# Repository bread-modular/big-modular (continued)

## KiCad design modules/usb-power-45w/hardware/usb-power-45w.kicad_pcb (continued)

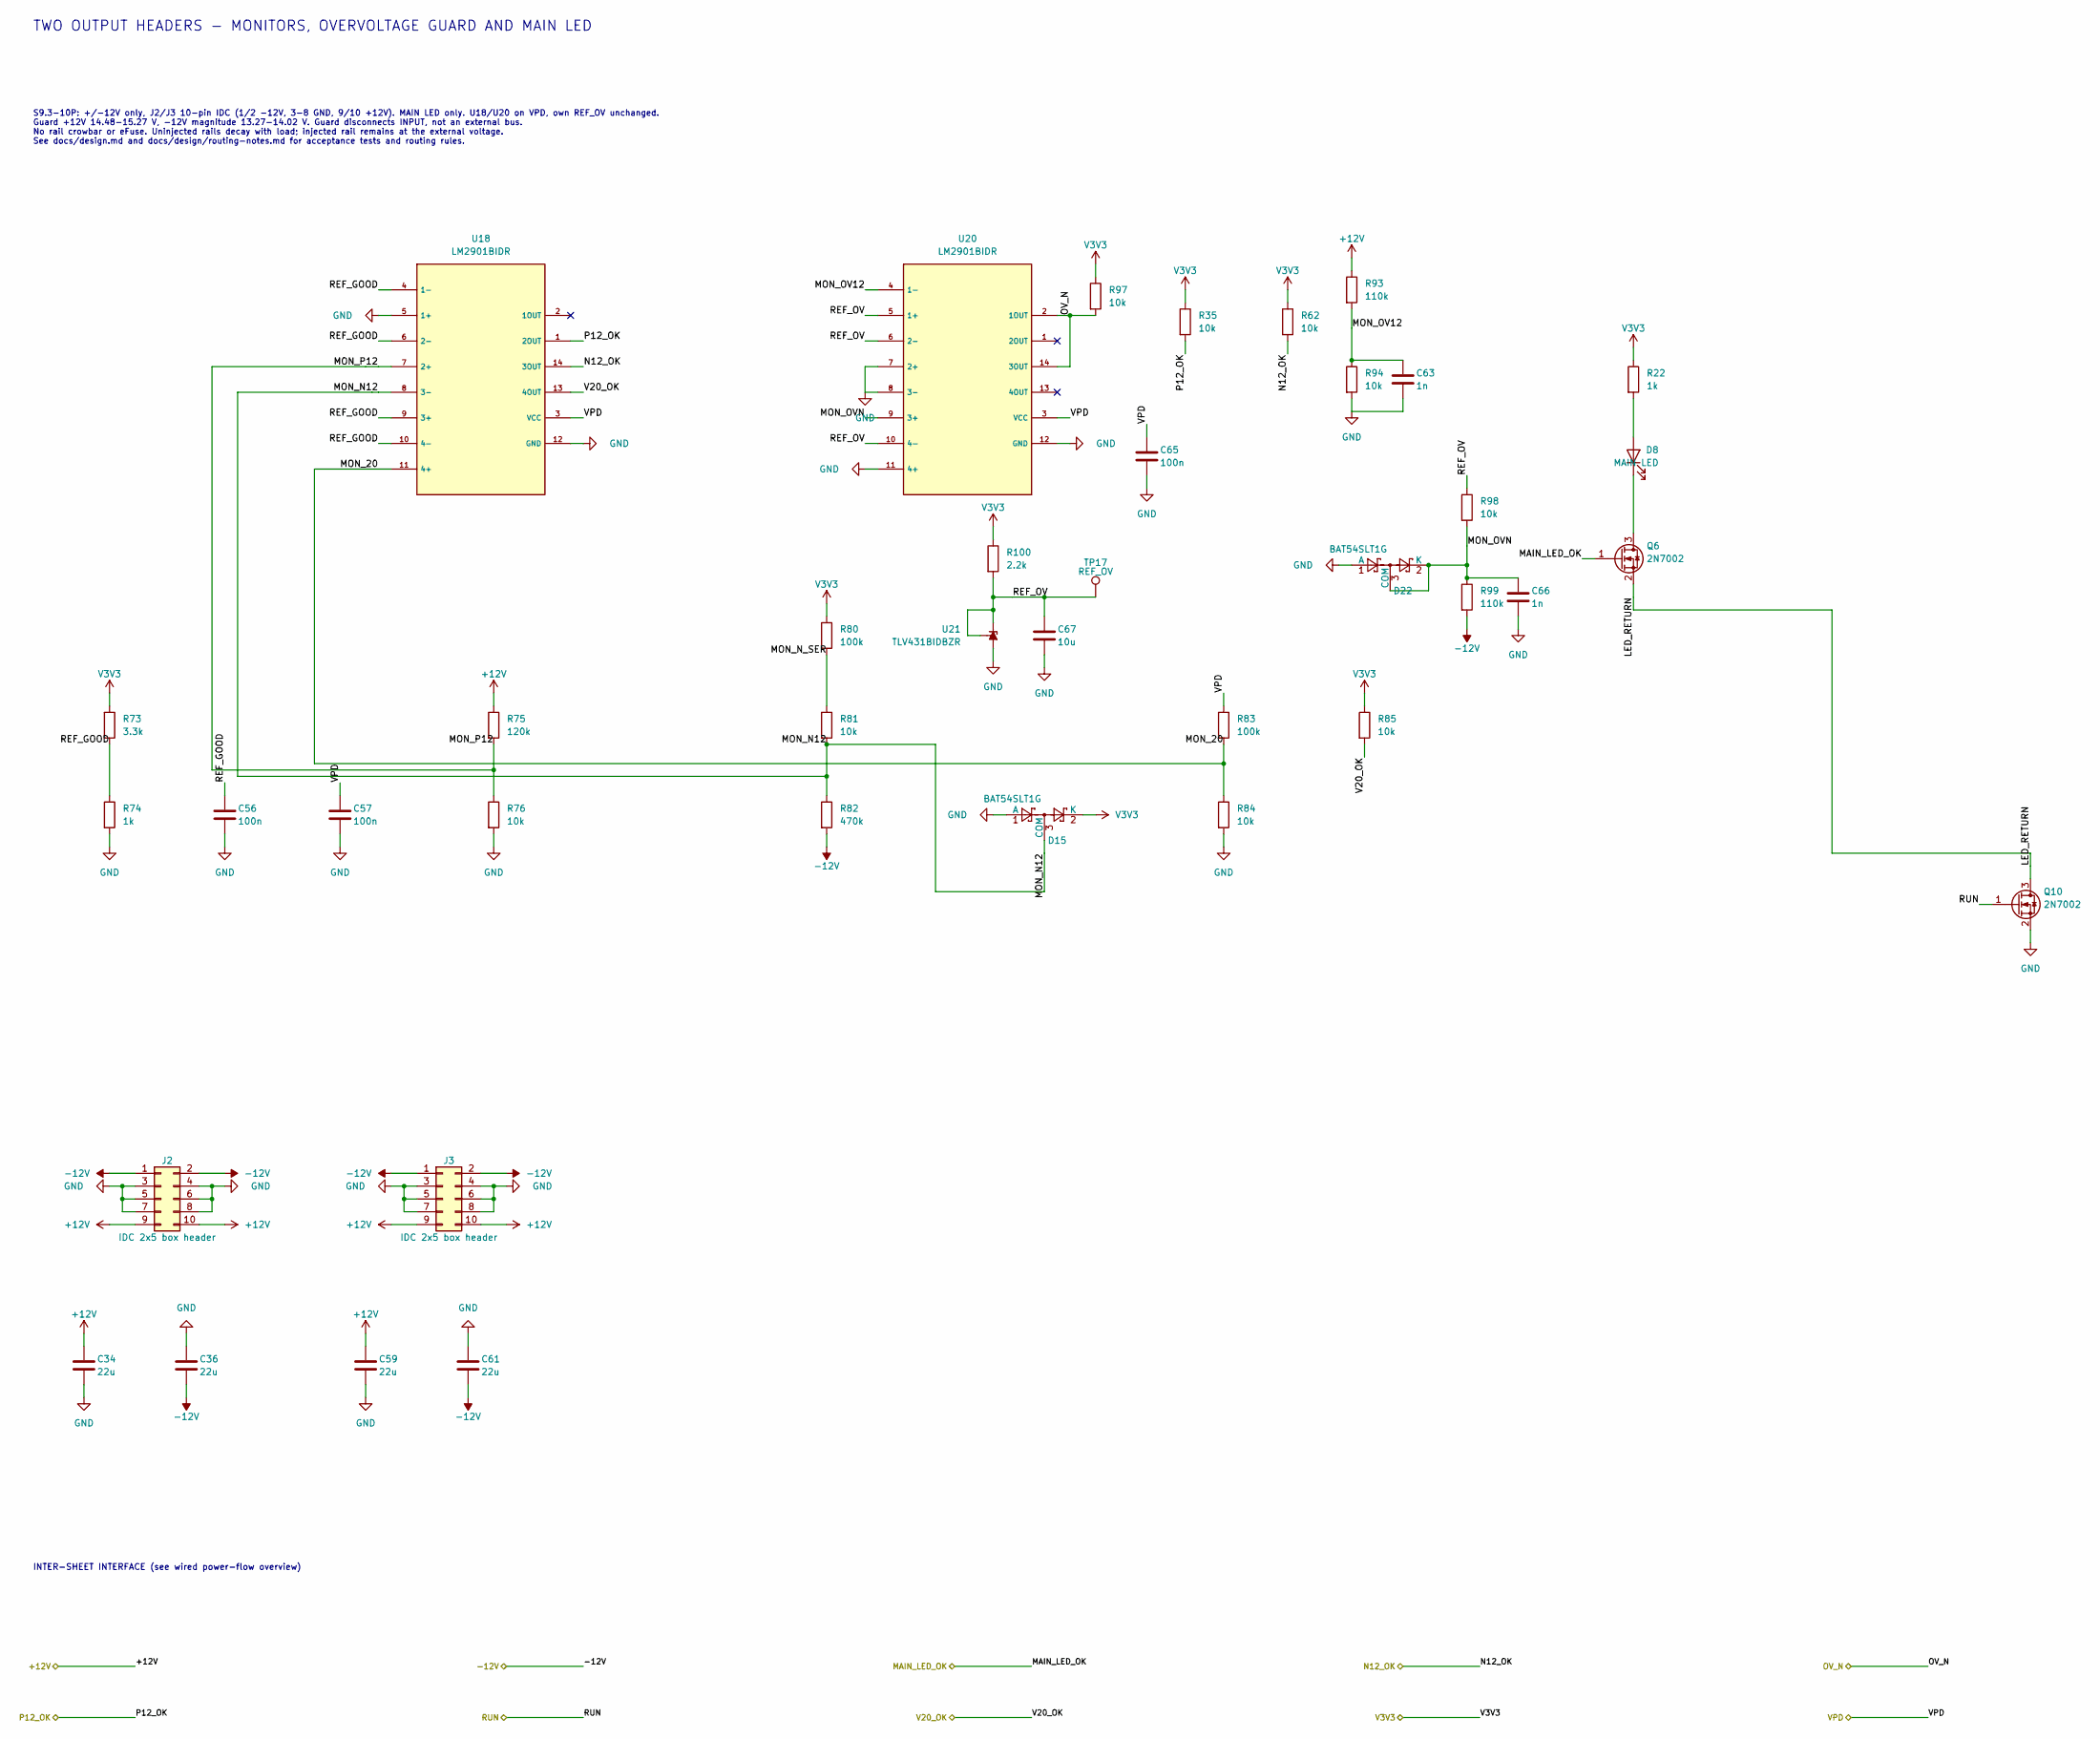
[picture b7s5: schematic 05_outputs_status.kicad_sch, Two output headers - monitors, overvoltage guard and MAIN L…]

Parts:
C34, C36, C59, C61: 22u; C_1206_3216Metric; Voltage 25V; MPN CL31A226KAHNNNE; LCSC C12891
C56, C57, C65: 100n; C_0603_1608Metric; Voltage 50V; MPN CC0603KRX7R9BB104; LCSC C14663
C63, C66: 1n; C_0603_1608Metric; Voltage 50V; MPN CL10B102KB8NNNC; LCSC C1588
C67: 10u; C_0603_1608Metric; Voltage 10V; MPN CL10A106KP8NNNC; LCSC C19702
D8: MAIN LED; LED_D3.0mm_Horizontal_O1.27mm_Z2.0mm_Edge
D15, D22: BAT54SLT1G; SOT-23; MPN BAT54SLT1G; LCSC C19726
J2, J3: IDC 2x5 box header; IDC-Header_2x05_P2.54mm_Vertical_Wurth_61201021621; MPN 61201021621
Q6, Q10: 2N7002; SOT-23; MPN 2N7002; LCSC C8545
R22, R74: 1k; R_0603_1608Metric; Tolerance 1%; MPN 0603WAF1001T5E; LCSC C21190
R35, R62, R76, R81, R84, R85, R97: 10k; R_0603_1608Metric; Tolerance 1%; MPN 0603WAF1002T5E; LCSC C25804
R73: 3.3k; R_0603_1608Metric; Tolerance 1%; MPN 0603WAF3301T5E; LCSC C22978
R75: 120k; R_0603_1608Metric; Tolerance 1%; MPN 0603WAF1203T5E; LCSC C25808
R80, R83: 100k; R_0603_1608Metric; Tolerance 1%; MPN 0603WAF1003T5E; LCSC C25803
R82: 470k; R_0603_1608Metric; Tolerance 1%; MPN 0603WAF4703T5E; LCSC C23178
R93, R99: 110k; R_0603_1608Metric; Tolerance 0.1%; MPN RT0603BRD07110KL; LCSC C326736
R94, R98: 10k; R_0603_1608Metric; Tolerance 0.1%; MPN RT0603BRD0710KL; LCSC C95204
R100: 2.2k; R_0603_1608Metric; Tolerance 1%; MPN 0603WAF2201T5E; LCSC C4190
TP17: REF_OV; TestPoint_Pad_D1.0mm
U18, U20: LM2901BIDR; SOIC-14_3.9x8.7mm_P1.27mm; MPN LM2901BIDR; LCSC C22427890
U21: TLV431BIDBZR; SOT-23; MPN TLV431BIDBZR; LCSC C398375

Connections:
+12V: C34.1, C59.1, J2.9, J2.10, J3.9, J3.10, R75.1, R93.1; also elsewhere on the board
-12V: C36.2, C61.2, J2.1, J2.2, J3.1, J3.2, R82.2, R99.2; also elsewhere on the board
/MAIN_LED_OK: Q6.1 (G); also elsewhere on the board
/N12_OK: R62.2, U18.14 (3OUT); also elsewhere on the board
/OV_N: R97.2, U20.2 (1OUT), U20.14 (3OUT); also elsewhere on the board
/P12_OK: R35.2, U18.1 (2OUT); also elsewhere on the board
/RUN: Q10.1 (G); also elsewhere on the board
/Two output headers - monitors, overvoltage guard and MAIN LED/LED_RETURN: Q6.2 (S), Q10.3 (D)
/Two output headers - monitors, overvoltage guard and MAIN LED/MON_20: R83.2, R84.1, U18.11 (4+)
/Two output headers - monitors, overvoltage guard and MAIN LED/MON_N12: D15.3 (COM), R81.2, R82.1, U18.8 (3-)
/Two output headers - monitors, overvoltage guard and MAIN LED/MON_N_SER: R80.2, R81.1
/Two output headers - monitors, overvoltage guard and MAIN LED/MON_OV12: C63.1, R93.2, R94.1, U20.4 (1-)
/Two output headers - monitors, overvoltage guard and MAIN LED/MON_OVN: C66.1, D22.2 (K), D22.3 (COM), R98.2, R99.1, U20.9 (3+)
/Two output headers - monitors, overvoltage guard and MAIN LED/MON_P12: R75.2, R76.1, U18.7 (2+)
/Two output headers - monitors, overvoltage guard and MAIN LED/REF_GOOD: C56.1, R73.2, R74.1, U18.4 (1-), U18.6 (2-), U18.9 (3+), U18.10 (4-)
/Two output headers - monitors, overvoltage guard and MAIN LED/REF_OV: C67.1, R98.1, R100.2, TP17.1 (1_1), U20.5 (1+), U20.6 (2-), U20.10 (4-), U21.1 (REF), U21.2 (K)
/V20_OK: R85.2, U18.13 (4OUT); also elsewhere on the board
/VPD: C57.1, C65.1, R83.1, U18.3 (VCC), U20.3 (VCC); also elsewhere on the board
GND: C34.2, C36.1, C56.2, C57.2, C59.2, C61.1, C63.2, C65.2, C66.2, C67.2, D15.1 (A), D22.1 (A), J2.3, J2.4, J2.5, J2.6, J2.7, J2.8, J3.3, J3.4, J3.5, J3.6, J3.7, J3.8, Q10.2 (S), R74.2, R76.2, R84.2, R94.2, U18.5 (1+), U18.12 (GND), U20.7 (2+), U20.8 (3-), U20.11 (4+), U20.12 (GND), U21.3 (A); also elsewhere on the board
unnamed: D8.2 (A), R22.2
unnamed: D8.1 (K), Q6.3 (D)
V3V3: D15.2 (K), R22.1, R35.1, R62.1, R73.1, R80.1, R85.1, R97.1, R100.1; also elsewhere on the board

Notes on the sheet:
TWO OUTPUT HEADERS - MONITORS, OVERVOLTAGE GUARD AND MAIN LED
INTER-SHEET INTERFACE (see wired power-flow overview)
S9.3-10P: +/-12V only, J2/J3 10-pin IDC (1/2 -12V, 3-8 GND, 9/10 +12V). MAIN LED only. U18/U20 on VPD, own REF_OV unchanged. Guard +12V 14.48-15.27 V, -12V magnitude 13.27-14.02 V. Guard disconnects INPUT, not an external bus. No rail crowbar or eFuse. Uninjected rails decay with load; injected rai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

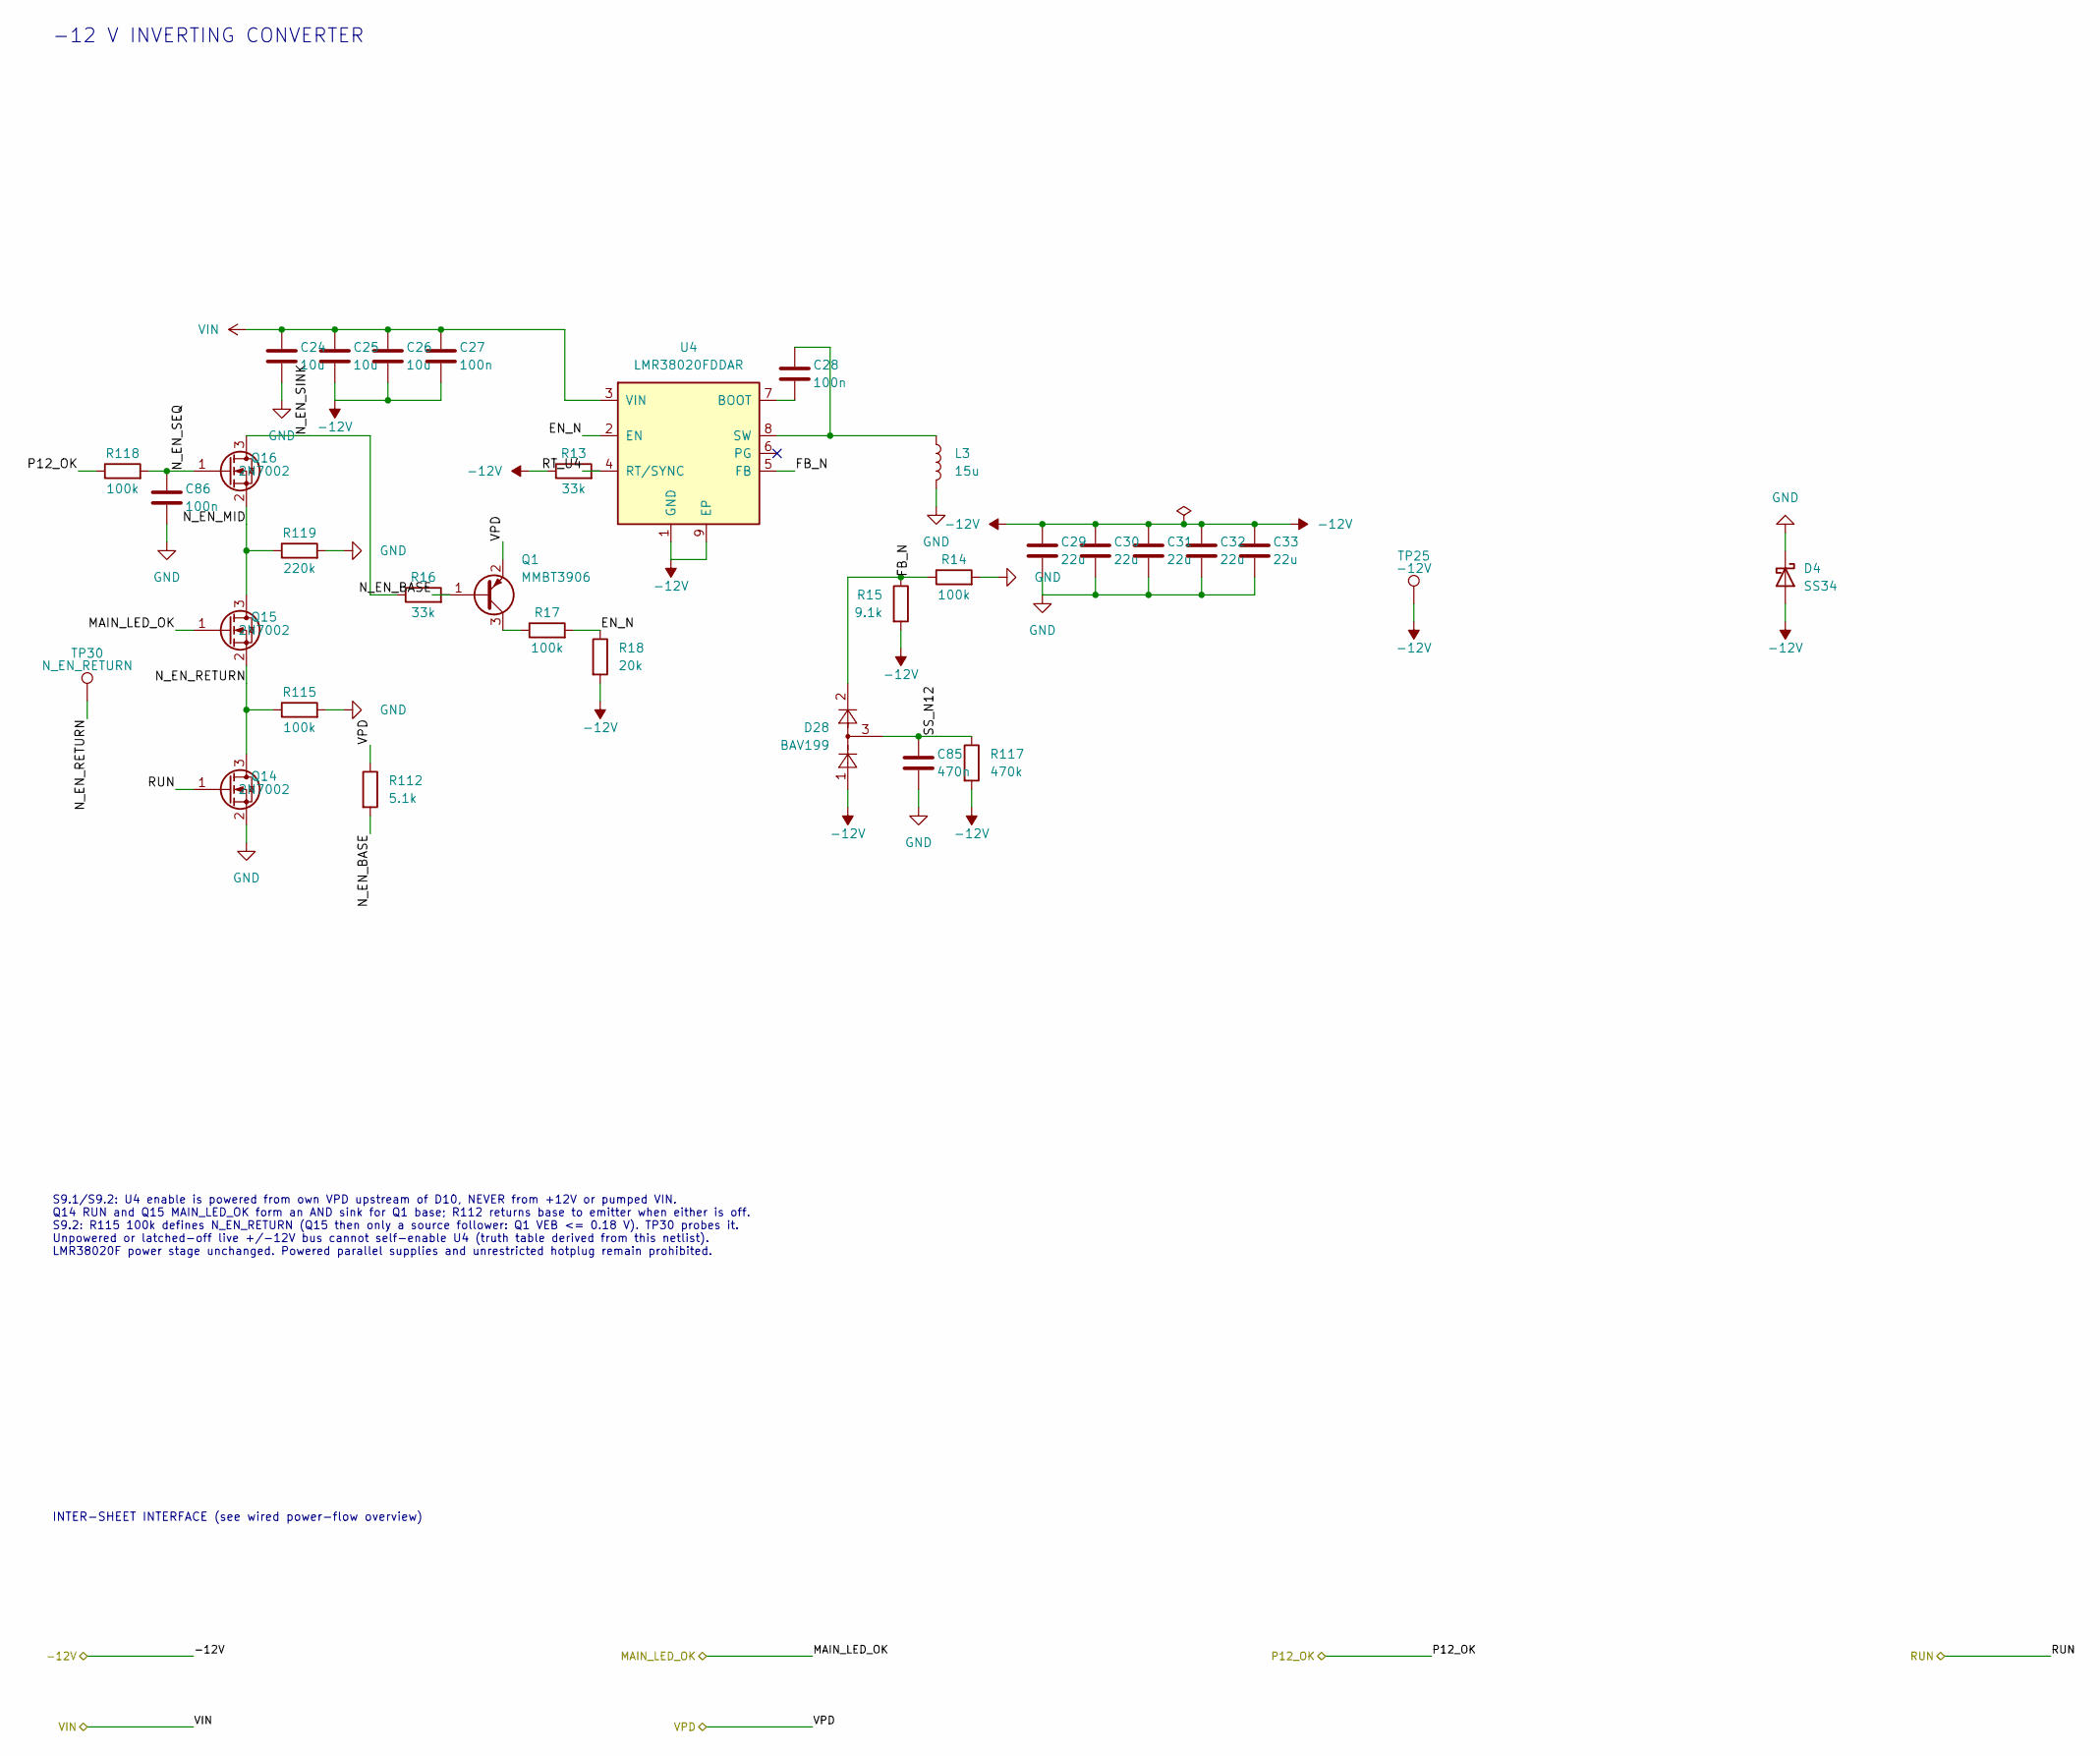
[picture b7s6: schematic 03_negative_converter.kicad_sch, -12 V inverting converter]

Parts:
C24, C25, C26: 10u; C_1206_3216Metric; Voltage 50V; MPN CL31A106KBHNNNE; LCSC C13585
C27, C28, C86: 100n; C_0603_1608Metric; Voltage 50V; MPN CC0603KRX7R9BB104; LCSC C14663
C29, C30, C31, C32, C33: 22u; C_1206_3216Metric; Voltage 25V; MPN CL31A226KAHNNNE; LCSC C12891
C85: 470n; C_0603_1608Metric; Voltage 25V; MPN CL10B474KA8NNNC; LCSC C1623
D4: SS34; D_SMA; MPN SS34; LCSC C8678
D28: BAV199; SOT-23; MPN BAV199LT1G; LCSC C145516
L3: 15u; L_SLO1040H6R8MTT; MPN SLO1040H150MTT; LCSC C182184
Q1: MMBT3906; SOT-23; MPN MMBT3906LT1G; LCSC C53444
Q14, Q15, Q16: 2N7002; SOT-23; MPN 2N7002; LCSC C8545
R13, R16: 33k; R_0603_1608Metric; Tolerance 1%; MPN 0603WAF3302T5E; LCSC C4216
R14, R17, R115, R118: 100k; R_0603_1608Metric; Tolerance 1%; MPN 0603WAF1003T5E; LCSC C25803
R15: 9.1k; R_0603_1608Metric; Tolerance 1%; MPN 0603WAF9101T5E; LCSC C23260
R18: 20k; R_0603_1608Metric; Tolerance 1%; MPN 0603WAF2002T5E; LCSC C4184
R112: 5.1k; R_0603_1608Metric; Tolerance 1%; MPN 0603WAF5101T5E; LCSC C23186
R117: 470k; R_0603_1608Metric; Tolerance 1%; MPN 0603WAF4703T5E; LCSC C23178
R119: 220k; R_0603_1608Metric; Tolerance 1%; MPN 0603WAF2203T5E; LCSC C22961
TP25: -12V; TestPoint_Pad_D1.5mm
TP30: N_EN_RETURN; TestPoint_Pad_D1.5mm
U4: LMR38020FDDAR; TI_SO-PowerPAD-8_NoViaInPad; MPN LMR38020FDDAR; LCSC C5149193

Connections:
-12V: C25.2, C26.2, C27.2, C29.1, C30.1, C31.1, C32.1, C33.1, D4.2 (A), D28.1 (A), R13.1, R15.2, R18.2, R117.2, TP25.1 (1_1), U4.1 (GND), U4.9 (EP); also elsewhere on the board
/-12 V inverting converter/EN_N: R17.2, R18.1, U4.2 (EN)
/-12 V inverting converter/FB_N: D28.2 (K), R14.1, R15.1, U4.5 (FB)
/-12 V inverting converter/N_EN_BASE: Q1.1 (B), R16.2, R112.2
/-12 V inverting converter/N_EN_MID: Q15.3 (D), Q16.2 (S), R119.1
/-12 V inverting converter/N_EN_RETURN: Q14.3 (D), Q15.2 (S), R115.1, TP30.1 (1_1)
/-12 V inverting converter/N_EN_SEQ: C86.1, Q16.1 (G), R118.2
/-12 V inverting converter/N_EN_SINK: Q16.3 (D), R16.1
/-12 V inverting converter/RT_U4: R13.2, U4.4 (RT/SYNC)
/-12 V inverting converter/SS_N12: C85.1, D28.3 (COM), R117.1
/MAIN_LED_OK: Q15.1 (G); also elsewhere on the board
/P12_OK: R118.1; also elsewhere on the board
/RUN: Q14.1 (G); also elsewhere on the board
/VPD: Q1.2 (E), R112.1; also elsewhere on the board
GND: C24.2, C29.2, C30.2, C31.2, C32.2, C33.2, C85.2, C86.2, D4.1 (K), L3.2, Q14.2 (S), R14.2, R115.2, R119.2; also elsewhere on the board
unnamed: Q1.3 (C), R17.1
unnamed: C28.2, U4.7 (BOOT)
unnamed: C28.1, L3.1, U4.8 (SW)
VIN: C24.1, C25.1, C26.1, C27.1, U4.3 (VIN); also elsewhere on the board

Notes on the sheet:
-12 V INVERTING CONVERTER
INTER-SHEET INTERFACE (see wired power-flow overview)
S9.1/S9.2: U4 enable is powered from own VPD upstream of D10, NEVER from +12V or pumped VIN. Q14 RUN and Q15 MAIN_LED_OK form an AND sink for Q1 base; R112 returns base to emitter when either is off. S9.2: R115 100k defines N_EN_RETURN (Q15 then only a source follower: Q1 VEB <= 0.18 V). TP30 probe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

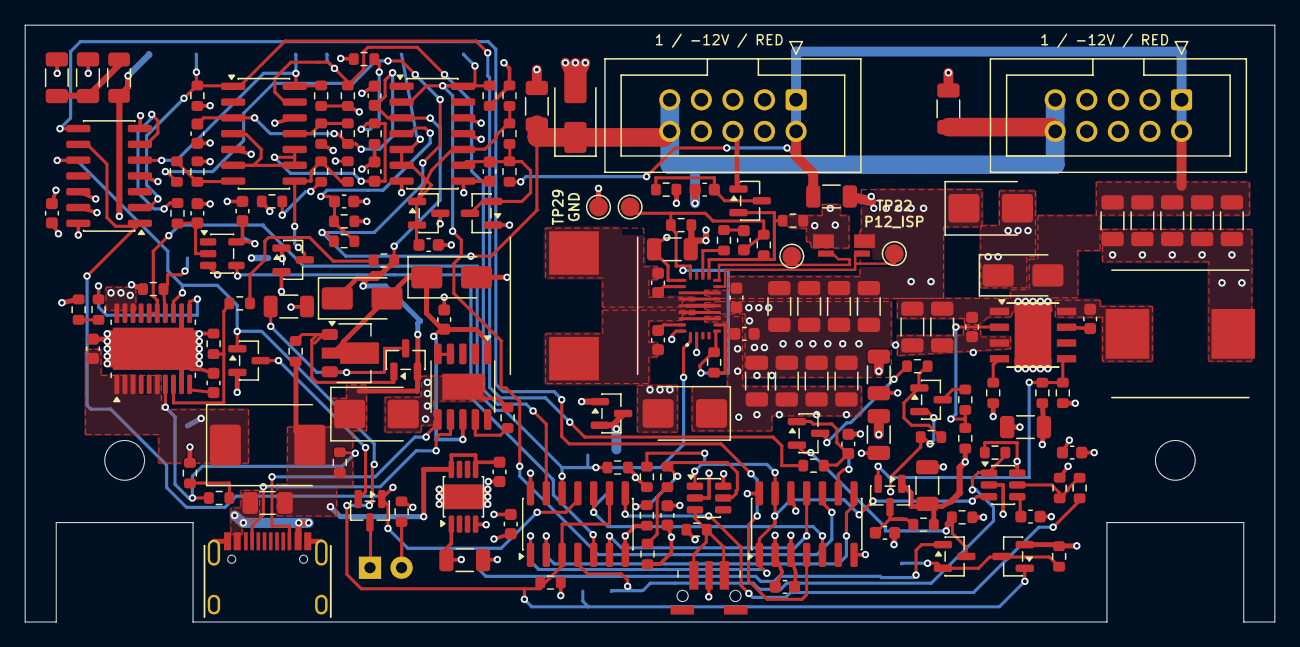
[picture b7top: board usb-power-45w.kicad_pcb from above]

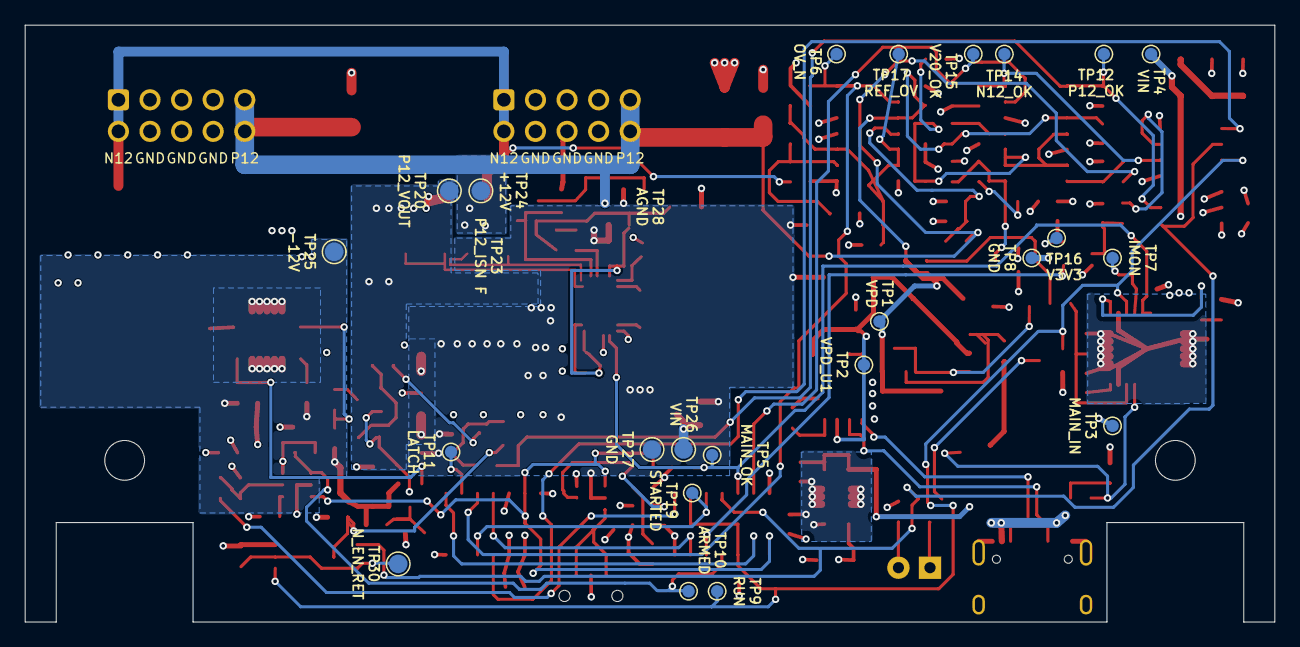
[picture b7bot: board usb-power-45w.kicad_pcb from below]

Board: 4 copper layers, 100.5 x 48.0 mm, 185 parts (23 on the bottom side), 84 nets.

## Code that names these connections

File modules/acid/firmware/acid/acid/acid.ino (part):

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// ----------------------------------------------------------------------------
// ACID — Bread Modular MCO + ENV on one ATtiny1616 (../../docs/research.md 3).
//
//   * MCO (BM 1.0.1, as modules/low): MIDI note-on sets tone 1 (PB4) and the
//     detuned tone 2 (PB5); DETUNE (PB0) puts tone 2 0..12 semitones below.
//   * ENV (BM 1.2.1): MIDI note on/off is the gate of the envelope on the DAC
//     (PA6 -> ENV_CV: SVF CV normal and ENV OUT). ATTACK (PA1, hold in HR) and
//     RELEASE (PA2) set the times, plus MIDI CC22 / CC75 as BM. MODE (PC0,
//     a click) cycles HR / AR / ASR, stored in EEPROM; the selected model's
//     LED (PC1 / PA4 / PA5) follows the envelope: its brightness tracks the
//     envelope level, up to 10 %; after power-up or a MODE change it is lit
//     at 10 % for 1 s to show the selection.
//   * REC (PC2 / LED PC3): 4-bar ATTACK/RELEASE motion recorder on MIDI clock
//     (shared lib/CvRecorder, as the 8bit crash): click to record (LED blinks),
//     after 4 bars it loops (LED solid), click again for the live knobs.
// ----------------------------------------------------------------------------

// JP1 on the ACID carrier picks the MIDI input path (set by ../../jumper.sh):
//   P (protected) = 8bit / MIDI V2 NPN front end, which inverts the UART data -> 1
//   D (direct)    = jack tip straight to PB3, as Bread Modular             -> 0
#ifndef MIDI_RX_INVERT
#error "MIDI_RX_INVERT must be set: build with ../../compile.sh p|d"
#endif

#define DETUNE_INPUT_PIN PIN_PB0
#define PIN_CV1          PIN_PA1   // ATTACK knob (hold time in HR)
#define PIN_CV2          PIN_PA2   // RELEASE knob
#define MODE_BUTTON_PIN  PIN_PC0   // envelope model (BM ENV algo button)
#define LED_HR           PIN_PC1
#define LED_AR           PIN_PA4
#define LED_ASR          PIN_PA5
#define REC_BUTTON_PIN   PIN_PC2   // BM ENV gate-mode button
#define REC_LED_PIN      PIN_PC3

#define ALGO_HOLD_RELEASE 0
#define ALGO_ATTACK_RELEASE 1
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#define KNOB_READ_MS 2             // knob reads off the envelope's hot loop

// MODE LED brightness: TCA0 in split mode (TCB0/TCB1 are the tones, TCD0 is
// millis), 20 MHz / 256 / 256 = 305 Hz, duty = count / 256. PA4 (WO4, HCMP1)
// and PA5 (WO5, HCMP2) are hardware PWM. PC1 has no TCA output, so the low
// counter switches it in software (LCMP0 on, LUNF off); those two interrupts
// run only while the HR LED is lit.
#define LED_MAX_PERCENT 10         // brightness at full envelope level
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EnvelopeGenerator *envelope;

ToggleMode algoMode(MODE_BUTTON_PIN, 1, 3);        // EEPROM index 1, as BM
CvRecorder recorder(REC_BUTTON_PIN, REC_LED_PIN);

const uint8_t modeLeds[3] = {LED_HR, LED_AR, LED_ASR};

float detunedSemitones = 0;
uint16_t liveCV1 = 0;              // ATTACK / RELEASE knobs (recorder input)
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int modCV2 = 0;                    // MIDI CC75 (release time)

bool midiGate = false;
byte gateNote = 0;                 // note that holds the gate
byte selectedLed = 0;              // index into modeLeds
unsigned long modeShownAt = 0;     // millis() of the last selection change

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  TCA0.SPLIT.CTRLA = TCA_SPLIT_CLKSEL_DIV256_gc | TCA_SPLIT_ENABLE_bm;
}

// PC1 (HR) software PWM: the down-counting low counter matches LCMP0 =
// duty - 1, so PC1 is high for duty counts until the underflow.
ISR(TCA0_LCMP0_vect) {
  PORTC.OUTSET = PIN1_bm;
  TCA0.SPLIT.INTFLAGS = TCA_SPLIT_LCMP0_bm;
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
  uint8_t outputs = 0;
  if (duty && led == 1) {
    outputs = TCA_SPLIT_HCMP1EN_bm;    // PA4 (AR)
  } else if (duty && led == 2) {
    outputs = TCA_SPLIT_HCMP2EN_bm;    // PA5 (ASR)
  }
  TCA0.SPLIT.CTRLB = outputs;

  const bool soft = duty && led == 0;  // PC1 (HR)
  TCA0.SPLIT.INTCTRL = soft ? TCA_SPLIT_LUNF_bm | TCA_SPLIT_LCMP0_bm : 0;
  if (!soft) {
    PORTC.OUTCLR = PIN1_bm;
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}

void handleNoteOff(byte channel, byte note, byte velocity) {
  // Only the latest note closes the gate: an overlapping (legato) note keeps
  // the envelope open instead of releasing it under the held note.
  if (note == gateNote) {
    midiGate = false;
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  MIDI.begin(1);
#if MIDI_RX_INVERT
  // JP1 = P: the NPN input stage inverts the MIDI UART data, so invert
  // PB3 (RX) in the port before the USART samples it.
  PORTB.PIN3CTRL |= PORT_INVEN_bm;
#endif
  MIDI.setHandleNoteOn(handleNoteOn);
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  (void)analogRead(PIN_CV1);       // throwaway warm-up read
  readKnobs();

  // DAC0 setup for the envelope via the PA6 pin
  VREF.CTRLA |= VREF_DAC0REFSEL_4V34_gc; //this will force it to use VDD as the VREF
  VREF.CTRLB |= VREF_DAC0REFEN_bm;
  DAC0.CTRLA = DAC_ENABLE_bm | DAC_OUTEN_bm;
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
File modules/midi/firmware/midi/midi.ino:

/* Arduino ATTiny 1616 Pin Map

  0 - PA4
  1 - PA5
  2 - PA6
  3 - PA7
  4 - PB5
  5 - PB4
  6 - PB3, RX
  7 - PB2, TX
  8 - PB1
  9 - PB0
  10 - PC0
  11 - PC1
  12 - PC2
  13 - PC3
  14 - PA1
  15 - PA2
  16 - PA3
*/

#include "SimpleMIDI.h"
#include <SoftwareSerial.h>

// Hardware version, set by ../compile.sh / ../flash.sh (v1 | v2 | v2-direct).
//   1 = V1 (hardware/v1): Bread Modular V1 direct input, JP1 -> PB3.
//   2 = V2 (hardware/v2): protected NPN input (Q1). It inverts the UART, so
//       PB3 needs PORT_INVEN (like the Bread Modular midi-2.0 6N137 firmware).
#ifndef MIDI_HW_VERSION
#error "MIDI_HW_VERSION is not set: build with ./compile.sh v1|v2|v2-direct"
#endif

// Invert RX (PB3). Defaults from the version; v2-direct sets 0 for a V2 board
// with JP2 bridged 2-3 (MIDI_IN straight to PB3, the V1 debug path).
#ifndef MIDI_RX_INVERT
#if MIDI_HW_VERSION == 1
#define MIDI_RX_INVERT 0
#elif MIDI_HW_VERSION == 2
#define MIDI_RX_INVERT 1
#else
#error "MIDI_HW_VERSION must be 1 or 2"
#endif
#endif

// Compile-time MIDI channel start (1-indexed).
// Default: respond to incoming MIDI channels 1-8.
// Override via a .config file (e.g. MIDI_CHAN_START=9 → channels 9-16).
#ifndef MIDI_CHAN_START
#define MIDI_CHAN_START 1
#endif

#define MIDI_CHAN_OFFSET (MIDI_CHAN_START - 1)

#define PIN_RX 6 // PB3
#define PIN_TX 7 // PB2

// Define the Gate Pins
#define GATE_PIN_01 10 // PC0
#define GATE_PIN_02 11 // PC1
#define GATE_PIN_03 12 // PC2
#define GATE_PIN_04 13 // PC3
#define GATE_PIN_05 14 // PA1
#define GATE_PIN_06 15 // PA2
#define GATE_PIN_07 16 // PA3
#define GATE_PIN_08 0 // PA4

// Define IMIDI Pins
#define IMIDI_PIN_01 1 // PA5
#define IMIDI_PIN_02 2 // PA6
#define IMIDI_PIN_03 3 // PA7
#define IMIDI_PIN_04 4 // PB5
#define IMIDI_PIN_05 5 // PB4
#define IMIDI_PIN_06 8 // PB1
#define IMIDI_PIN_07 9 // PB0

// Channel LED brightness, as the MCC bank LEDs: software PWM on the LED pins
// (no hardware PWM on all of them). TCB0 ticks at 20 kHz; LED_PWM_STEPS ticks
// = 200 Hz PWM, LED_ON_STEPS of them on.
#define LED_PWM_STEPS 100
#define LED_ON_STEPS 3      // 3 % brightness
#define LED_PORTC_MASK (PIN0_bm | PIN1_bm | PIN2_bm | PIN3_bm)  // CH1-CH4
#define LED_PORTA_MASK (PIN1_bm | PIN2_bm | PIN3_bm | PIN4_bm)  // CH5-CH8
constexpr uint16_t LED_TCB_COMPARE = (F_CPU / 2) / 20000 - 1;
volatile uint8_t ledMaskC = 0;  // PORTC bits of the lit channel LEDs
volatile uint8_t ledMaskA = 0;  // PORTA bits of the lit channel LEDs

// Create a MIDI object
SimpleMIDI MIDI;

SoftwareSerial midiSerialArray[] = {
    SoftwareSerial(-1, IMIDI_PIN_01),
    SoftwareSerial(-1, IMIDI_PIN_02),
    SoftwareSerial(-1, IMIDI_PIN_03),
    SoftwareSerial(-1, IMIDI_PIN_04),
    SoftwareSerial(-1, IMIDI_PIN_05),
    SoftwareSerial(-1, IMIDI_PIN_06),
    SoftwareSerial(-1, IMIDI_PIN_07),
};

int getGatePin(int id) {
  switch (id) {
    case 0:
      return GATE_PIN_01;
    case 1:
      return GATE_PIN_02;
    case 2:
      return GATE_PIN_03;
    case 3:
      return GATE_PIN_04;
    case 4:
      return GATE_PIN_05;
    case 5:
      return GATE_PIN_06;
    case 6:
      return GATE_PIN_07;
    case 7:
      return GATE_PIN_08;
    default:
      return -1;
  }
}

// Map an incoming MIDI channel (0-15) to a local output/gate index (0-7),
// or -1 if the channel is outside the configured range.
int getOutputIndex(byte channel) {
  int idx = (int)channel - MIDI_CHAN_OFFSET;
  if (idx < 0 || idx > 7) {
    return -1;
  }
  return idx;
}

// Port bit of channel LED `id` (0-7): CH1-CH4 on PC0-PC3, CH5-CH8 on PA1-PA4.
uint8_t getLedBit(int id) {
  return id < 4 ? (1 << id) : (1 << (id - 3));
}

void setLed(int id, bool on) {
  const uint8_t bit = getLedBit(id);
  volatile uint8_t &mask = id < 4 ? ledMaskC : ledMaskA;
  uint8_t sreg = SREG;
  cli();
  if (on) {
    mask |= bit;
  } else {
    mask &= ~bit;
    if (id < 4) {
      PORTC.OUTCLR = bit;
    } else {
      PORTA.OUTCLR = bit;
    }
  }
  SREG = sreg;
}

void setupLedPwm() {
  TCB0.CTRLA = TCB_CLKSEL_CLKDIV2_gc;  // 10 MHz
  TCB0.CTRLB = TCB_CNTMODE_INT_gc;     // periodic interrupt
  TCB0.CCMP = LED_TCB_COMPARE;
  TCB0.INTCTRL = TCB_CAPT_bm;
  TCB0.CTRLA |= TCB_ENABLE_bm;
}

ISR(TCB0_INT_vect) {
  static uint8_t step = 0;
  if (++step >= LED_PWM_STEPS) {
    step = 0;
  }
  if (step < LED_ON_STEPS) {
    PORTC.OUTSET = ledMaskC;
    PORTA.OUTSET = ledMaskA;
  } else {
    PORTC.OUTCLR = LED_PORTC_MASK;
    PORTA.OUTCLR = LED_PORTA_MASK;
  }
  TCB0.INTFLAGS = TCB_CAPT_bm;
}

void sendMIDI(byte channel, byte status, byte data1, byte data2) {
  if (channel == 7) {
    Serial.write(status); // Send the status byte
    Serial.write(data1);  // Send the first data byte
    Serial.write(data2);  // Send the second data byte
    return;
  }

  int channelIndex = channel;
  if (channelIndex >= 0 && channelIndex < 7) {
    SoftwareSerial &serialCh = midiSerialArray[channelIndex];
    serialCh.write(status); // Send the status byte
    serialCh.write(data1);  // Send the first data byte
    serialCh.write(data2);  // Send the second data byte
  }
}

void sendMIDIRealtime(byte realtimeByte) {
  for (int i = 0; i < 7; i++) {
    midiSerialArray[i].write(realtimeByte);
  }

  // This is for the channel 8
  Serial.write(realtimeByte);
}

void setupGates() {
  for (int x = 0; x < 8; x = x + 1) {
    int gatePin = getGatePin(x);
    pinMode(gatePin, OUTPUT);
    digitalWrite(gatePin, LOW);
  }
  setupLedPwm();
}

void setupIMIDI() {
  pinMode(IMIDI_PIN_01, OUTPUT);
  pinMode(IMIDI_PIN_02, OUTPUT);
  pinMode(IMIDI_PIN_03, OUTPUT);
  pinMode(IMIDI_PIN_04, OUTPUT);
  pinMode(IMIDI_PIN_05, OUTPUT);
  pinMode(IMIDI_PIN_06, OUTPUT);
  pinMode(IMIDI_PIN_07, OUTPUT);

  for (int i = 0; i < 7; i++) {
    midiSerialArray[i].begin(31250); // Start each SoftwareSerial at MIDI baud rate
  }
}

void handleNoteOn(byte channel, byte note, byte velocity) {
  int idx = getOutputIndex(channel);
  if (idx == -1) {
    return;
  }

  setLed(idx, true);

  sendMIDI(idx, 0x90, note, velocity);
}

// Callback for Note Off messages
void handleNoteOff(byte channel, byte note, byte velocity) {
  int idx = getOutputIndex(channel);
  if (idx == -1) {
    return;
  }

  setLed(idx, false);

  sendMIDI(idx, 0x80, note, velocity);
}

// Callback for handling CC messages
void handleControlChange(byte channel, byte controller, byte value) {
  int idx = getOutputIndex(channel);
  if (idx == -1) {
    return;
  }

  sendMIDI(idx, 0xB0, controller, value);
}

void handleRealtime(byte realtimeType) {
  sendMIDIRealtime(realtimeType);
}

void setup() {
  setupGates();

  // Initialize the MIDI library
  MIDI.begin(31250);
  MIDI.setNoteOnCallback(handleNoteOn);
  MIDI.setNoteOffCallback(handleNoteOff);
  MIDI.setControlChangeCallback(handleControlChange);
  MIDI.setRealtimeCallback(handleRealtime);

#if MIDI_RX_INVERT
  // V2 NPN input stage inverts the MIDI UART data, so tell the port to
  // invert PB3 (RX) before the USART samples it.
  PORTB.PIN3CTRL |= PORT_INVEN_bm;
#endif

  setupIMIDI();

  Serial.println("MIDI Listening Started!");
}

void loop() {
  MIDI.update();
}

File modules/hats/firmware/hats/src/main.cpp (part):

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// HATS S4 firmware (STM32G071C8T6 U2): Bread Modular NOISE + HIHAT on one
// MCU, plus the PWM CUTOFF vactrol and the shared 4-bar REC recorder.
//
//   PA4 DAC1_OUT1  white noise (BM NOISE, -> R6 / U4A, blue high-pass)
//   PA5 DAC1_OUT2  velocity (BM HIHAT)
//   PA2 / PA3      gate / open hat (BM HIHAT: notes > 60 open)
//   PA1 ADC_IN1    NOISE TONE knob (RV1)
//   PA6 ADC_IN6    CUTOFF knob (RV3)
//   PB0 TIM3_CH3   CUTOFF vactrol LED PWM (R51 -> U11), 31.25 kHz, dithered
//   PB4 / PB5      REC button (pull-up) / REC LED (R48 -> D6)
//   PB7 USART1_RX  MIDI 31250 baud, all channels; RXINV for JP1 = P
//
//   REC (shared CvRecorder): lane 1 CUTOFF, lane 2 NOISE TONE, 4 bars on
//   MIDI clock. MIDI CC 74 x 8 adds to NOISE TONE (BM).
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
// JP1 on the HATS carrier picks the MIDI input path (set by ../jumper.sh):
//   P (protected) = NPN front end (Q1), which inverts the UART data -> 1
//   D (direct)    = jack tip straight to PB7, as Bread Modular     -> 0
#ifndef MIDI_RX_INVERT
#error "MIDI_RX_INVERT must be set: build with ../compile.sh p|d"
#endif

#define GATE_PIN       PIN_PA(2)
#define OPEN_HAT_PIN   PIN_PA(3)
#define REC_BUTTON_PIN PIN_PB(4)
#define REC_LED_PIN    PIN_PB(5)

#define ADC_CH_TONE    1   // PA1
#define ADC_CH_CUTOFF  6   // PA6

static const uint32_t SYSCLK_HZ = 64000000;

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static hats::PwmDither dither;
static hats::MidiParser midi;
static hats::HihatOut hihat;
static CvRecorder recorder(REC_BUTTON_PIN, REC_LED_PIN);

static uint8_t cc74 = 0;
static uint16_t liveCutoff = 0;   // knobs, 0..1023 (recorder input)
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
static void gpioInit() {
    RCC->IOPENR |= RCC_IOPENR_GPIOAEN | RCC_IOPENR_GPIOBEN;
    pinMode(GATE_PIN, OUTPUT);
    pinMode(OPEN_HAT_PIN, OUTPUT);
    digitalWrite(GATE_PIN, LOW);
    digitalWrite(OPEN_HAT_PIN, LOW);
    setMode(GPIOA, 1, 3);   // NOISE TONE, analog
    setMode(GPIOA, 6, 3);   // CUTOFF, analog
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    return (uint16_t)(ADC1->DR >> 2);                // 12 -> 10 bit, as BM analogRead
}

// One scan: PA1 (TONE) then PA6 (CUTOFF).
static void readKnobs() {
    ADC1->CR |= ADC_CR_ADSTART;
    liveTone = adcNext();
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            default:
                continue;
        }
        digitalWrite(GATE_PIN, hihat.gate ? HIGH : LOW);
        digitalWrite(OPEN_HAT_PIN, hihat.open ? HIGH : LOW);
        DAC1->DHR12R2 = hats::dac12(hihat.velocity);
    }
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
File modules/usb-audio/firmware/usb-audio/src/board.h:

// MCU board: clocks, SysTick, pins that are not I2S/I2C, USBHS interrupt.
//
// Pin map (modules/usb-audio/Code.md, MCU board S1):
//   PB6/PB7  USBHS D-/D+          PA9   VBUS sense (10k/20k divider)
//   PB13/PB12/PB15  I2S2 CK/WS/SD (slave RX <- codec SDOUT)
//   PB3/PA15/PB5    I2S3 CK/WS/SD (slave TX -> codec SDIN)
//   PB10/PB11 I2C2 SCL/SDA        PB14  codec RST (10k pull-down on the carrier)
#ifndef BOARD_H_
#define BOARD_H_

#include <stdbool.h>
#include <stddef.h>
#include <stdint.h>

#include "ch32v30x.h"

void board_init(void);
uint32_t board_millis(void);
void board_delay_ms(uint32_t ms);
void board_delay_us(uint32_t us);
bool board_vbus_present(void);
void board_codec_reset(bool asserted);
void board_serial(char *out, size_t len);
void board_reset(void);
// Reset into the DFU bootloader (../bootloader) for ../flash.sh.
void board_reset_to_dfu(void);
// Rewrite + verify the DFU bootloader from RAM (console `blwrite`). Stop I2S first.
bool board_write_bootloader(uint8_t const *img, uint32_t len);
// Settings page: the last 256 bytes of the application area, which the linker
// script leaves free (Makefile). The DFU bootloader erases only the pages it
// writes, so the page survives firmware updates; ../flash.sh --full erases it.
#define BOARD_SETTINGS_BYTES 256u
void const *board_settings(void);
// Erase the page and write `len` bytes (0: erase only), verified. Stop I2S first.
bool board_settings_write(void const *data, uint32_t len);
uint32_t board_crc32(void const *data, uint32_t len);
// Main loop: feeds the bootloader's watchdog and confirms a newly downloaded
// image once the host has kept it configured (../bootloader/src/boot.h).
void board_boot_task(bool configured);

// Critical section against the I2S DMA and USB processing handlers that keeps
// the USBHS capture interrupt (priority 0, board_init) running: masks the
// priorities >= 0x40 through the PFIC threshold.
static inline uint32_t board_irq_mask(void) {
  uint32_t const prev = PFIC->ITHRESDR;
  PFIC->ITHRESDR = 0x40;
  (void) PFIC->ITHRESDR;
  return prev;
}

static inline void board_irq_restore(uint32_t prev) {
  PFIC->ITHRESDR = prev;
}

#endif

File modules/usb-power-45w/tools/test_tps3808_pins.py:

"""TPS3808G01 pin-identity regression (S6 had SENSE=3 / MR=5; TI DBV is MR=3 / SENSE=5).

Run from the repository root (needs kicad-cli; reads, never writes, the module):
  python3 -B -m unittest discover -s modules/usb-power-45w/tools -p 'test_*.py' -v

The old map was self-consistent: symbol, circuit table and verifier table all agreed.
These tests rebuild that state (circuit() and CRIT reverted too) and require the
manufacturer-derived check in verify_design.py to reject it on its own.
"""
import copy
import shutil
import subprocess
import sys
import tempfile
import unittest
import xml.etree.ElementTree as ET
from pathlib import Path
from unittest import mock

sys.path.insert(0, str(Path(__file__).resolve().parent))
import circuit45  # noqa: E402
import verify_design  # noqa: E402
from sexp import parse, nodes, one, walk  # noqa: E402

MODULE = Path(__file__).resolve().parents[1]
HW = MODULE / 'hardware'
OLD_COMMIT = '077905c'          # last commit with the swapped TPS3808 map
OLD_PINS = {'U10': {'1': 'RESET_N', '2': 'GND', '3': 'POR_SENSE', '4': None, '5': 'RESET_BTN_N', '6': 'V3V3'},
            'U11': {'1': 'START_READY', '2': 'GND', '3': 'START_SENSE', '4': 'START_CT', '5': 'RESET_N', '6': 'V3V3'}}
OLD_CRIT = {'U10': {1: 'RESET_N', 2: 'GND', 3: 'POR_SENSE', 5: 'RESET_BTN_N', 6: 'V3V3'},
            'U11': {1: 'START_READY', 2: 'GND', 3: 'START_SENSE', 4: 'START_CT', 5: 'RESET_N', 6: 'V3V3'}}


def export_netlist(sch, out):
    subprocess.run(['kicad-cli', 'sch', 'export', 'netlist', '--format', 'kicadxml', '-o', str(out), str(sch)],
                   check=True, stdout=subprocess.DEVNULL)
    return out


def symbol_pins(lib_file, name='TPS3808G01'):
    sym = {s[1]: s for s in nodes(parse(Path(lib_file).read_text()), 'symbol')}[name]
    plain = lambda n: n[:-2] if n.endswith('_N') else n
    return {one(p, 'number')[1]: plain(one(p, 'name')[1]) for p in walk(sym, 'pin')}


def old_circuit(pre_s7=False):
    parts = copy.deepcopy(circuit45.circuit())
    for p in parts:
        if p['ref'] in OLD_PINS:
            p['pins'] = dict(OLD_PINS[p['ref']])
    if pre_s7:   # the committed pre-fix hardware still has the second parallel header J3 (removed in S7)
        for p in parts:                  # and the unnamed U4 RT net (S7 names it RT_U4)
            p['pins'] = {n: ('_RT_U4' if v == 'RT_U4' else v) for n, v in p['pins'].items()}
        j2 = next(p for p in parts if p['ref'] == 'J2')
        j2['fields']['Note'] = PRE_S7_HEADER_NOTE
        for k in PRE_S7_J2_DROPPED:                 # S7 R2 added the Wurth MPN/Manufacturer; 077905c had none
            assert j2['fields'].pop(k, None), k
        j3 = copy.deepcopy(j2)
        j3['ref'] = 'J3'
        parts.append(j3)
    return parts


PRE_S7_J2_DROPPED = ('MPN', 'Manufacturer')
PRE_S7_FP = {'IDC16': 'IDC-Header_2x08_P2.54mm_Vertical'}   # 077905c footprint; S7 R2 pins the Wurth 61201621621 land
PRE_S7_HEADER_NOTE = ('Hand-soldered shrouded 16-pin box header, pin 1 = -12V (red stripe). J2 and J3 are in '
                      'parallel: use both cables above ~1.5 A per rail. CV/GATE (13-16) open')


def mutate(src, dst, swap_symbol, swap_nets):
    """swap_symbol: libpart and pin functions use the old SENSE=3/MR=5 names.
    swap_nets: U10/U11 pins 3 and 5 exchange nets (the old circuit table)."""
    tree = ET.parse(src)
    root = tree.getroot()
    if swap_symbol:
        lib = next(p for p in root.iter('libpart') if p.get('part') == 'TPS3808G01')
        names = {x.get('num'): x for x in lib.findall('pins/pin')}
        names['3'].set('name', 'SENSE')
        names['5'].set('name', 'MR_N')
    for node in root.iter('node'):
        if node.get('ref') in OLD_PINS and node.get('pin') in ('3', '5'):
            pin = node.get('pin')
            other = '5' if pin == '3' else '3'
            func = node.get('pinfunction').removesuffix('_' + pin)
            if swap_nets:                       # same net now reaches the other physical pin
                node.set('pin', other)
                pin = other
                if not swap_symbol:             # fixed symbol: the pin keeps its datasheet name
                    func = {'SENSE': 'MR_N', 'MR_N': 'SENSE'}[func]
            elif swap_symbol:                   # old symbol names on unchanged nets
                func = {'SENSE': 'MR_N', 'MR_N': 'SENSE'}[func]
            node.set('pinfunction', f'{func}_{pin}')
    tree.write(dst)
    return dst


@unittest.skipUnless(shutil.which('kicad-cli'), 'kicad-cli required')
class TPS3808PinIdentity(unittest.TestCase):
    @classmethod
    def setUpClass(cls):
        cls.tmp = Path(tempfile.mkdtemp(prefix='tps3808-pins-'))
        cls.netlist = export_netlist(HW / 'usb-power-45w-system.kicad_sch', cls.tmp / 'current.xml')

    @classmethod
    def tearDownClass(cls):
        shutil.rmtree(cls.tmp)

    def verify(self, netlist, hardware=HW, root=None):
        return verify_design.verify(netlist, hardware, hierarchy_root=root)

    def old_tables(self, pre_s7=False):
        crit = {**verify_design.CRIT, **OLD_CRIT}
        fp = {**verify_design.FP, **PRE_S7_FP} if pre_s7 else verify_design.FP
        return mock.patch.multiple(verify_design, circuit=lambda: old_circuit(pre_s7), CRIT=crit, FP=fp)

    def test_symbols_match_ti_table(self):
        self.assertEqual(verify_design.TPS3808_DBV, {'1': 'RESET', '2': 'GND', '3': 'MR', '4': 'CT', '5': 'SENSE', '6': 'VDD'})
        for lib in (MODULE / 'tools/USBPOWER45-src.kicad_sym', HW / 'USBPOWER45.kicad_sym'):
            self.assertEqual(symbol_pins(lib), verify_design.TPS3808_DBV, lib)

    def test_current_design_passes(self):
        self.assertTrue(self.verify(self.netlist)['exact_field_pin_NC_pad_parity'])

    def test_old_self_consistent_map_rejected(self):
        bad = mutate(self.netlist, self.tmp / 'old-both.xml', swap_symbol=True, swap_nets=True)
        with self.old_tables():
            with mock.patch.object(verify_design, 'check_tps3808'):   # without it the old map passes
                self.verify(bad)
            with self.assertRaisesRegex(AssertionError, 'TPS3808G01 symbol pin identity'):
                self.verify(bad)

    def test_fixed_symbol_with_old_nets_rejected(self):
        bad = mutate(self.netlist, self.tmp / 'old-nets.xml', swap_symbol=False, swap_nets=True)
        with self.old_tables(), self.assertRaisesRegex(AssertionError, 'TPS3808 role not on'):
            self.verify(bad)

    def test_old_symbol_with_fixed_nets_rejected(self):
        bad = mutate(self.netlist, self.tmp / 'old-symbol.xml', swap_symbol=True, swap_nets=False)
        with self.assertRaisesRegex(AssertionError, 'TPS3808G01 symbol pin identity'):
            self.verify(bad)

    def test_committed_old_hardware_rejected(self):
        """The real pre-fix native schematic, with its own circuit/CRIT tables restored."""
        repo = MODULE.parents[1]
        rel = MODULE.relative_to(repo) / 'hardware'
        ls = subprocess.run(['git', '-C', str(repo), 'ls-tree', '-r', '--name-only', OLD_COMMIT, str(rel)],
                            capture_output=True, text=True)
        if ls.returncode or not ls.stdout.strip():
            self.skipTest(f'git history {OLD_COMMIT} unavailable')
        old_hw = self.tmp / 'old/hardware'
        for name in ls.stdout.split():
            dst = old_hw / Path(name).relative_to(rel)
            dst.parent.mkdir(parents=True, exist_ok=True)
            dst.write_bytes(subprocess.run(['git', '-C', str(repo), 'show', f'{OLD_COMMIT}:{name}'],
                                           check=True, capture_output=True).stdout)
        old_root = old_hw / 'usb-power-45w.kicad_sch'     # historical filename of the S6 root at that commit
        old = export_netlist(old_root, self.tmp / 'old.xml')
        with self.old_tables(pre_s7=True):
            with mock.patch.object(verify_design, 'check_tps3808'):
                self.verify(old, old_hw, old_root)
            with self.assertRaisesRegex(AssertionError, 'TPS3808G01 symbol pin identity'):
                self.verify(old, old_hw, old_root)


if __name__ == '__main__':
    unittest.main()
